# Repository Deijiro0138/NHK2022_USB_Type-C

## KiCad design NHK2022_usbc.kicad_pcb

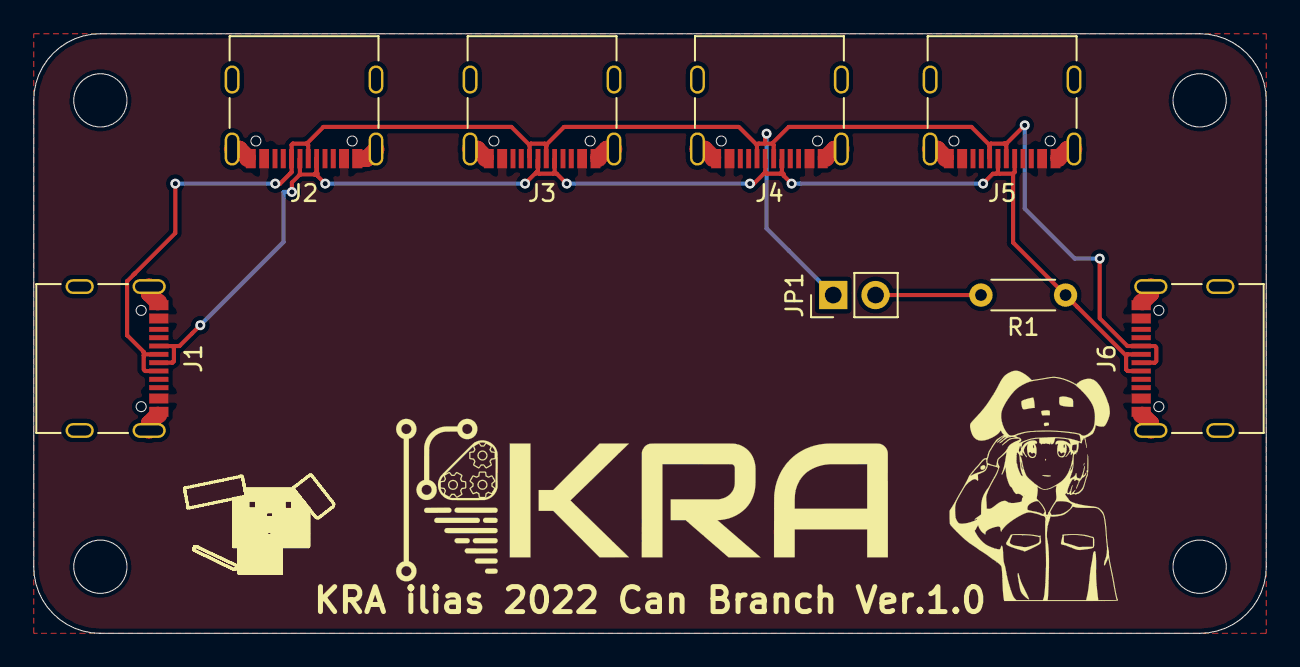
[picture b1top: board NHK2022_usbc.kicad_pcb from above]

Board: 2 copper layers, 74.0 x 36.0 mm, 9 parts (0 on the bottom side), 5 nets.

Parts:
J1, J2, J3, J4, J5, J6: USB_C_Receptacle_USB2.0; USB_C_Receptacle_Palconn_UTC16-G
JP1: Jumper_2_Open; PinHeader_1x02_P2.54mm_Vertical
R1: R; R_Axial_DIN0204_L3.6mm_D1.6mm_P5.08mm_Horizontal
ref**: val**; ROGIKEN

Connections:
D+: J1.A6, J1.B6, J2.A6, J2.B6, J3.A6, J3.B6, J4.A6, J4.B6, J5.A6, J5.B6, J6.A6, J6.B6, JP1.1
D-: J1.A7, J1.B7, J2.A7, J2.B7, J3.A7, J3.B7, J4.A7, J4.B7, J5.A7, J5.B7, J6.A7, J6.B7, R1.1
GND: J1.A1, J1.A12, J1.B1, J1.B12, J1.S1, J2.A1, J2.A12, J2.B1, J2.B12, J2.S1, J3.A1, J3.A12, J3.B1, J3.B12, J3.S1, J4.A1, J4.A12, J4.B1, J4.B12, J4.S1, J5.A1, J5.A12, J5.B1, J5.B12, J5.S1, J6.A1, J6.A12, J6.B1, J6.B12, J6.S1
unnamed: JP1.2, R1.2
VBUS: J1.A4, J1.A9, J1.B4, J1.B9, J2.A4, J2.A9, J2.B4, J2.B9, J3.A4, J3.A9, J3.B4, J3.B9, J4.A4, J4.A9, J4.B4, J4.B9, J5.A4, J5.A9, J5.B4, J5.B9, J6.A4, J6.A9, J6.B4, J6.B9

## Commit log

2022-04-09 Create pictures
